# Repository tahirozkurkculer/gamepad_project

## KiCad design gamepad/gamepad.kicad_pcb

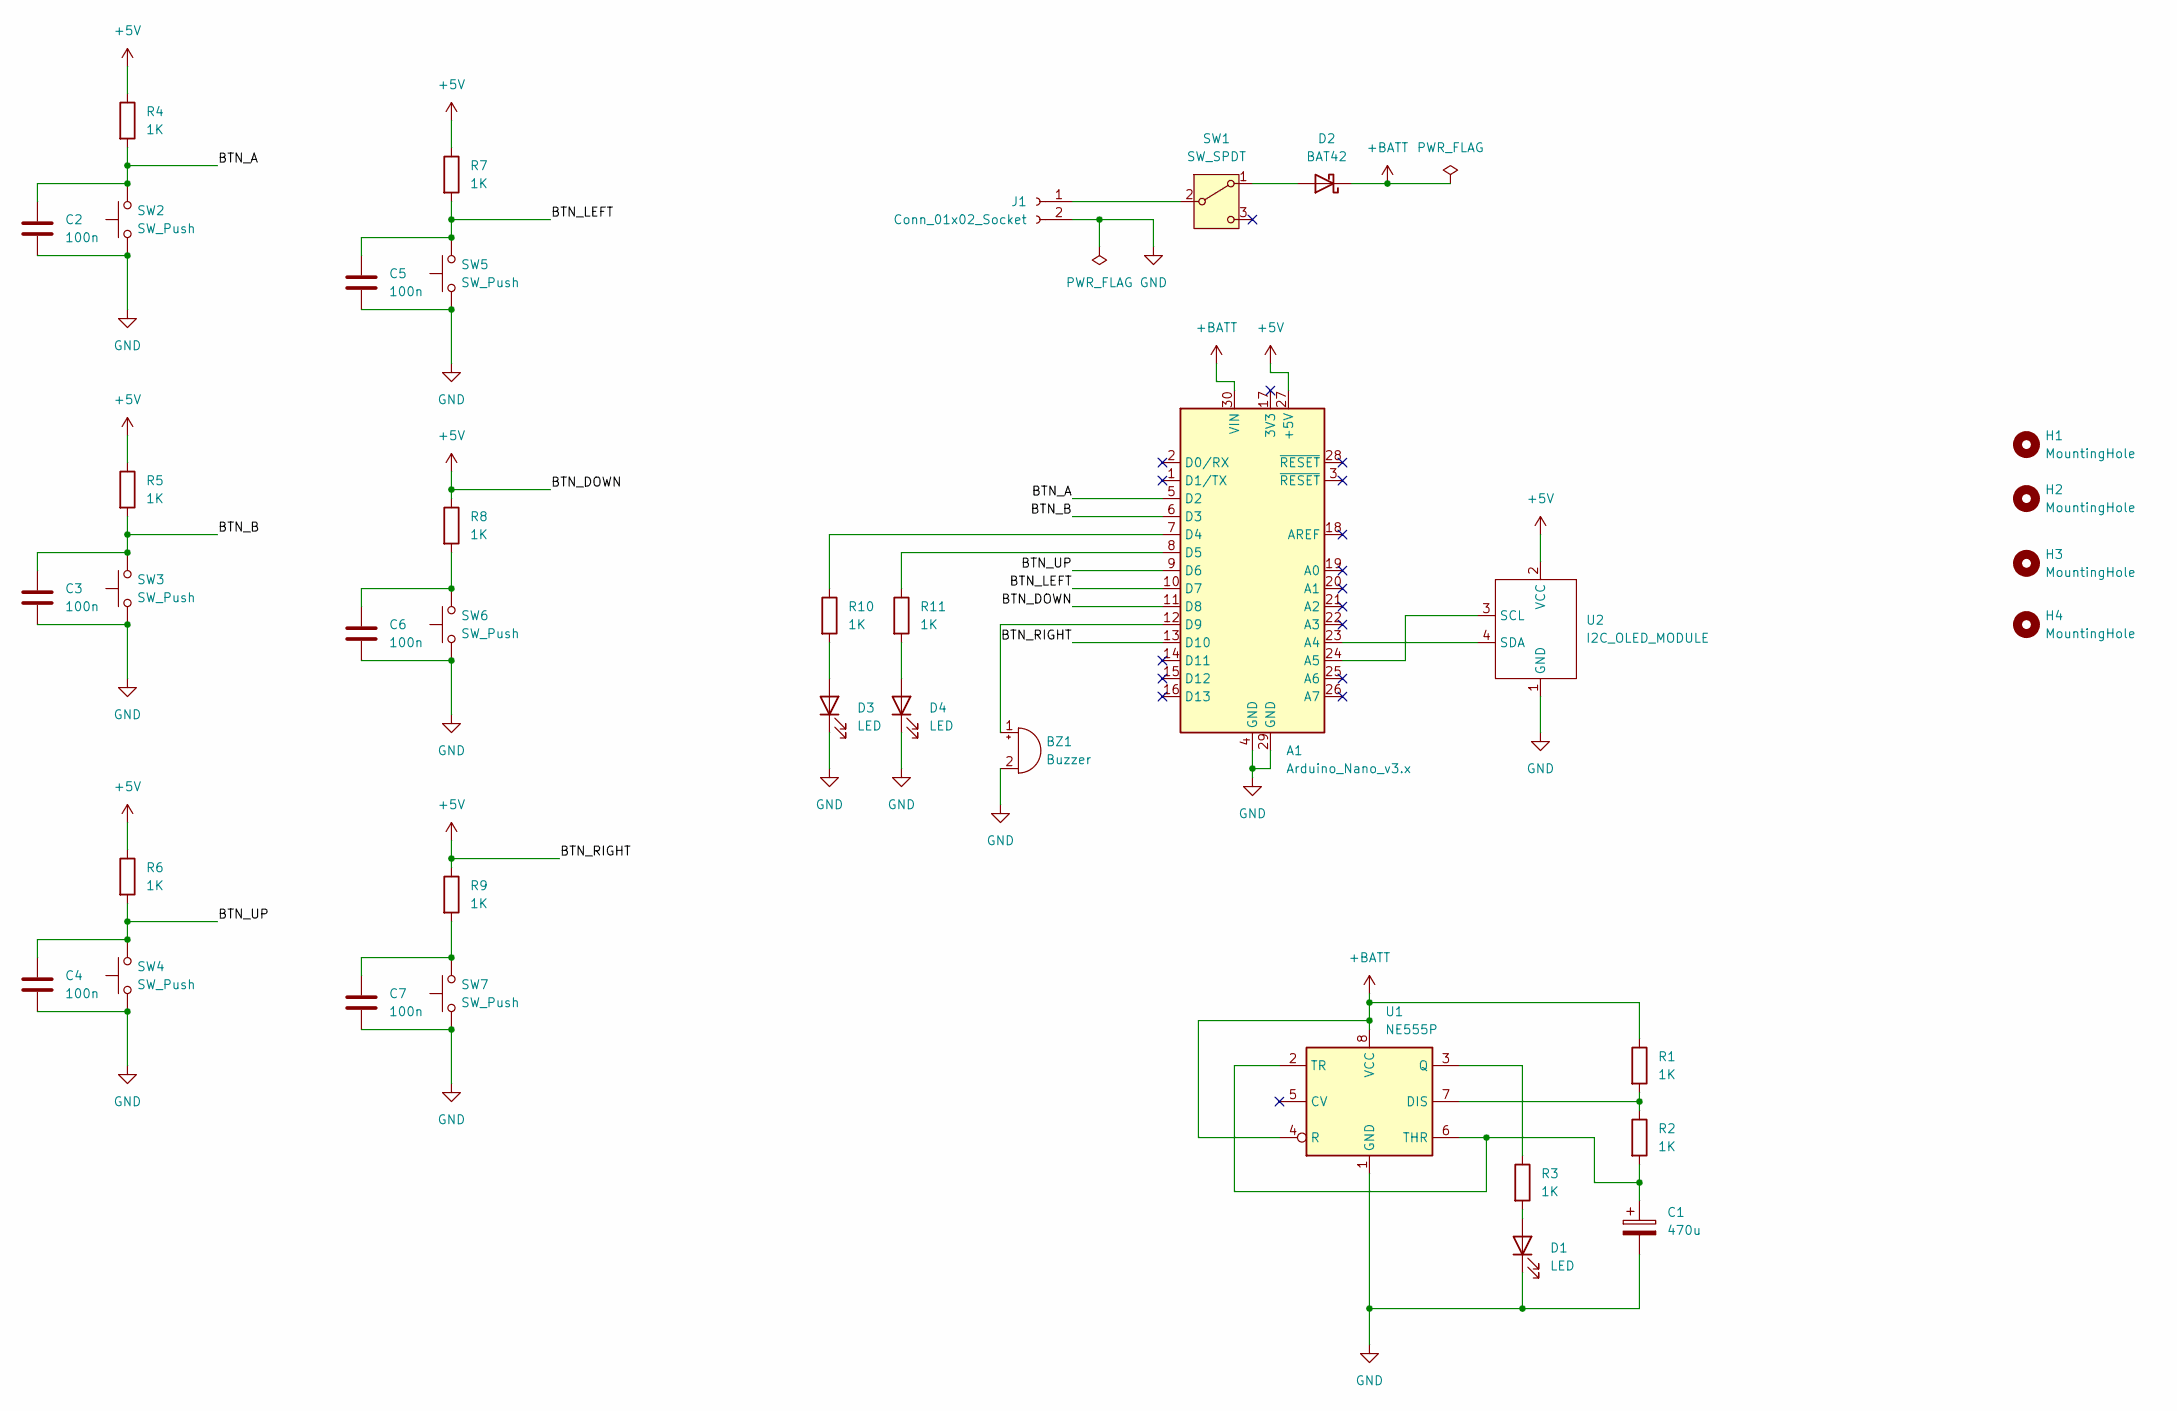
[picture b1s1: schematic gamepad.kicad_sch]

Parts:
A1: Arduino_Nano_v3.x; Arduino_Nano
BZ1: Buzzer; Buzzer_12x9.5RM7.6
C1: 470u; CP_Radial_D6.3mm_P2.50mm
C2, C3, C4, C5, C6, C7: 100n; C_Disc_D4.7mm_W2.5mm_P5.00mm
D1, D3, D4: LED; LED_D5.0mm
D2: BAT42; D_DO-35_SOD27_P7.62mm_Horizontal
H1, H2, H3, H4: MountingHole; MountingHole_2.5mm
J1: Conn_01x02_Socket; Molex_Micro-Latch_53254-0270_1x02_P2.00mm_Horizontal
R1, R2, R3, R4, R5, R6, R7, R8, R9, R10, R11: 1K; R_Axial_DIN0207_L6.3mm_D2.5mm_P7.62mm_Horizontal
SW1: SW_SPDT; spdt_slide_switch
SW2, SW3, SW4, SW5, SW6, SW7: SW_Push; SW_PUSH_6mm
U1: NE555P; DIP-8_W7.62mm
U2: I2C_OLED_MODULE; i2c_oled_module

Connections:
+5V: A1.11 (D8), A1.13 (D10), A1.27 (+5V), R4.1, R5.1, R6.1, R7.1, R8.1, R9.1, U2.2 (VCC)
+BATT: A1.30 (VIN), D2.1 (K), R1.1, U1.4 (R), U1.8 (VCC)
/BTN_A: A1.5 (D2), C2.1, R4.2, SW2.2
/BTN_B: A1.6 (D3), C3.1, R5.2, SW3.2
/BTN_LEFT: A1.10 (D7), C5.1, R7.2, SW5.2
/BTN_UP: A1.9 (D6), C4.1, R6.2, SW4.2
GND: A1.4 (GND), A1.29 (GND), BZ1.2 (-), C1.2, C2.2, C3.2, C4.2, C5.2, C6.2, C7.2, D1.1 (K), D3.1 (K), D4.1 (K), J1.2, SW2.1, SW3.1, SW4.1, SW5.1, SW6.1, SW7.1, U1.1 (GND), U2.1 (GND)
unnamed: A1.23 (A4), U2.4 (SDA)
unnamed: A1.24 (A5), U2.3 (SCL)
unnamed: A1.7 (D4), R10.1
unnamed: A1.8 (D5), R11.1
unnamed: A1.12 (D9), BZ1.1 (+)
unnamed: C6.1, R8.2, SW6.2
unnamed: C7.1, R9.2, SW7.2
unnamed: D1.2 (A), R3.2
unnamed: D2.2 (A), SW1.1 (A)
unnamed: D3.2 (A), R10.2
unnamed: D4.2 (A), R11.2
unnamed: J1.1, SW1.2 (B)
unnamed: R1.2, R2.1, U1.7 (DIS)
unnamed: R3.1, U1.3 (Q)
unnamed: C1.1, R2.2, U1.2 (TR), U1.6 (THR)

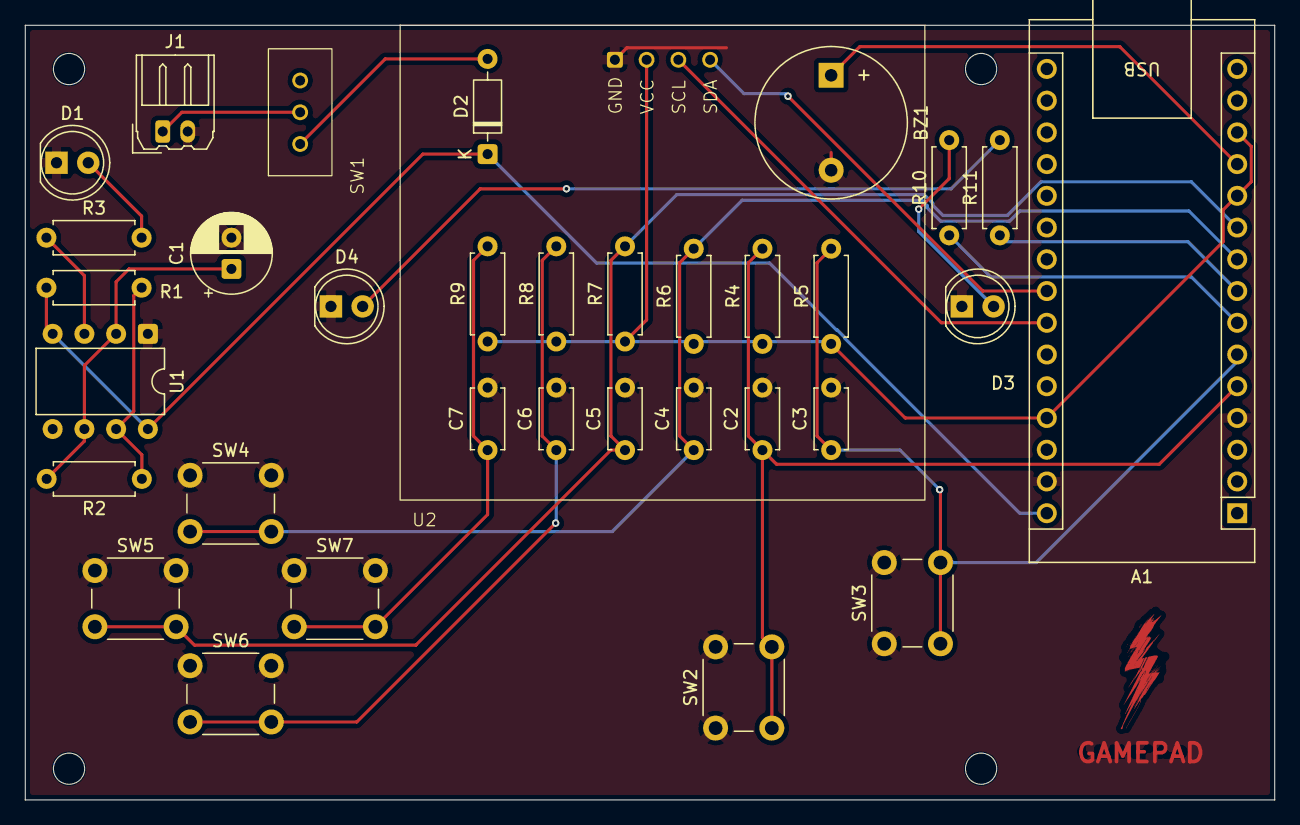
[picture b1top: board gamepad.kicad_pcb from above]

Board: 2 copper layers, 100.0 x 62.0 mm, 38 parts (0 on the bottom side), 22 nets.
